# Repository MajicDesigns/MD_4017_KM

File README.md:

# MD_4017_KM

_An more full featured alternative to this library can be found as the MD_UISwitch_4017KM Class in the MD_UISwitch Libray found [here](https://github.com/MajicDesigns/MD_UISwitch)._

This is a library to manage the keyswitch matrix implemented using a 4017 as described in the articles at 
* [EDN Design #1](http://www.edn.com/design/power-management/4413677/Connect-a-4-3-matrix-keyboard-to-a-microcontroller-using-two-I-O-pins)
* [EDN Design #2](http://www.edn.com/design/components-and-packaging/4408027/Read-10-or-more-switches-using-only-two-I-O-pins-of-a-microcontroller)

Using a 4017 IC, this library implements a method for reading many open/closed switches using only three digital I/O pins (Clock, Reset and DataIn}).

The library
* Allows definition of the size of the keyswitch matrix
* Manages the scanning of the 4017 to read the matrix
* Detects the transition from OFF state to ON state for each key
* Implements software enabled debounce and software auto repeat

Eagle CAD files for a 3x3 version of the matrix are included, as well as the articles referenced in the URL above.

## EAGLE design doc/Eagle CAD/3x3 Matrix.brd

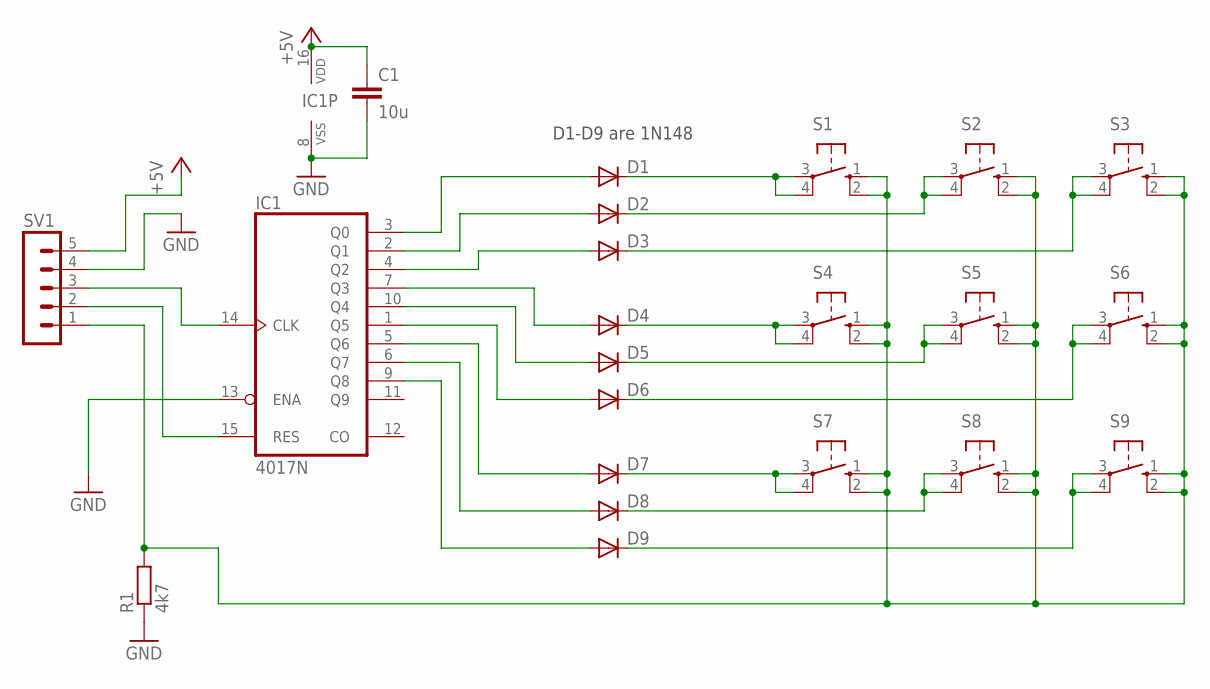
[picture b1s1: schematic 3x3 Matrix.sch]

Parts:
C1: 10u; C025-024X044
D1, D2, D3, D4, D5, D6, D7, D8, D9: 1N4148DO35-7; DO35-7
IC1: 4017N; DIL16
R1: 4k7; 0207/10
S1, S2, S3, S4, S5, S6, S7, S8, S9: 10-XX; B3F-10XX
SV1: MA05-1

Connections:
+5V: C1.1, IC1.16 (VDD), SV1.5
GND: C1.2, IC1.8 (VSS), IC1.13 (ENA), R1.1, SV1.4
unnamed: D1.A, IC1.3 (Q0)
unnamed: D2.A, IC1.2 (Q1)
unnamed: D3.A, IC1.4 (Q2)
unnamed: D9.A, IC1.9 (Q8)
unnamed: D8.A, IC1.6 (Q7)
unnamed: D7.A, IC1.5 (Q6)
unnamed: D6.A, IC1.1 (Q5)
unnamed: D5.A, IC1.10 (Q4)
unnamed: D4.A, IC1.7 (Q3)
unnamed: IC1.15 (RES), SV1.2
unnamed: D1.C, S1.3, S1.4 (P1)
unnamed: D2.C, S2.3, S2.4 (P1)
unnamed: R1.2, S1.1 (S), S1.2 (S1), S2.1 (S), S2.2 (S1), S3.1 (S), S3.2 (S1), S4.1 (S), S4.2 (S1), S5.1 (S), S5.2 (S1), S6.1 (S), S6.2 (S1), S7.1 (S), S7.2 (S1), S8.1 (S), S8.2 (S1), S9.1 (S), S9.2 (S1), SV1.1
unnamed: D3.C, S3.3, S3.4 (P1)
unnamed: D4.C, S4.3, S4.4 (P1)
unnamed: D5.C, S5.3, S5.4 (P1)
unnamed: D6.C, S6.3, S6.4 (P1)
unnamed: D7.C, S7.3, S7.4 (P1)
unnamed: D8.C, S8.3, S8.4 (P1)
unnamed: D9.C, S9.3, S9.4 (P1)
unnamed: IC1.14 (CLK), SV1.3

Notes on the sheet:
D1-D9 are 1N148

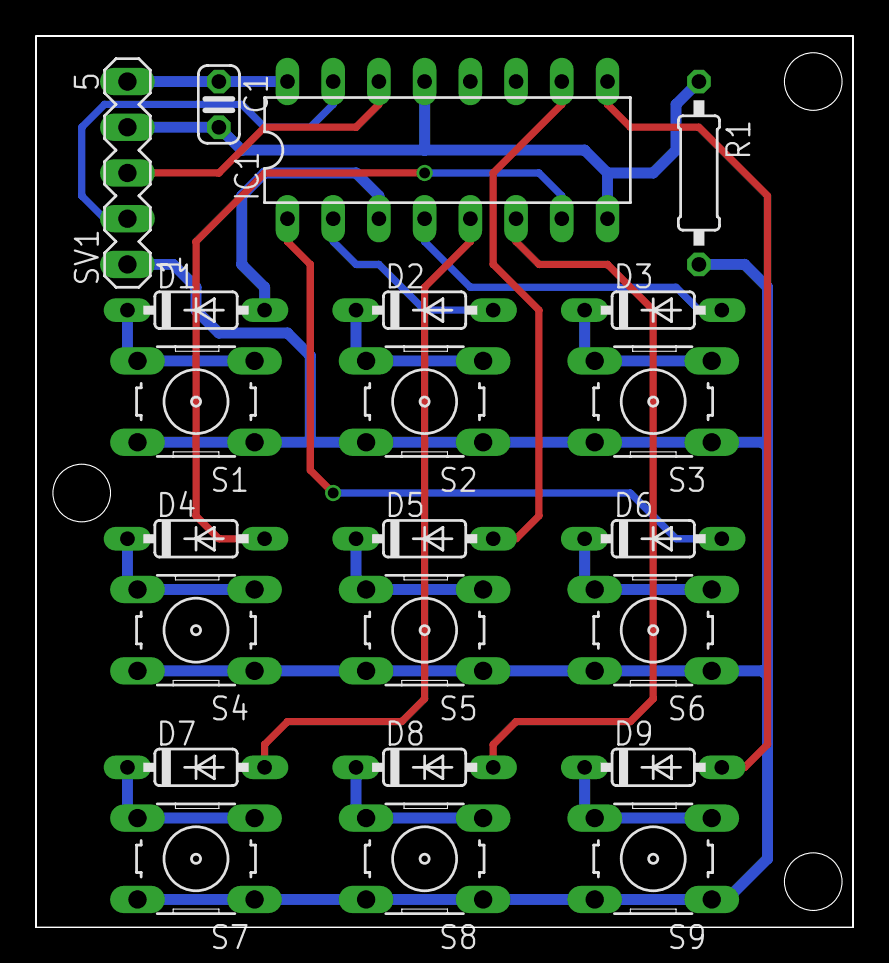
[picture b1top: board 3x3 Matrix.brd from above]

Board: 2 copper layers, 45.4 x 49.5 mm, 22 parts (0 on the bottom side), 23 nets.

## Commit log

2016-11-14 Under Version Control
2016-11-14 README edit
2017-01-12 Updated homepage URL
2017-09-16 Use correct separator in keywords.txt
    The Arduino IDE requires the use of a tab separator between the name and identifier. Without this tab the keyword is not highlighted.
    Reference: https://github.com/arduino/Arduino/wiki/Arduino-IDE-1.5:-Library-specification#keywords
2017-09-23 Local mods keyword.txt
